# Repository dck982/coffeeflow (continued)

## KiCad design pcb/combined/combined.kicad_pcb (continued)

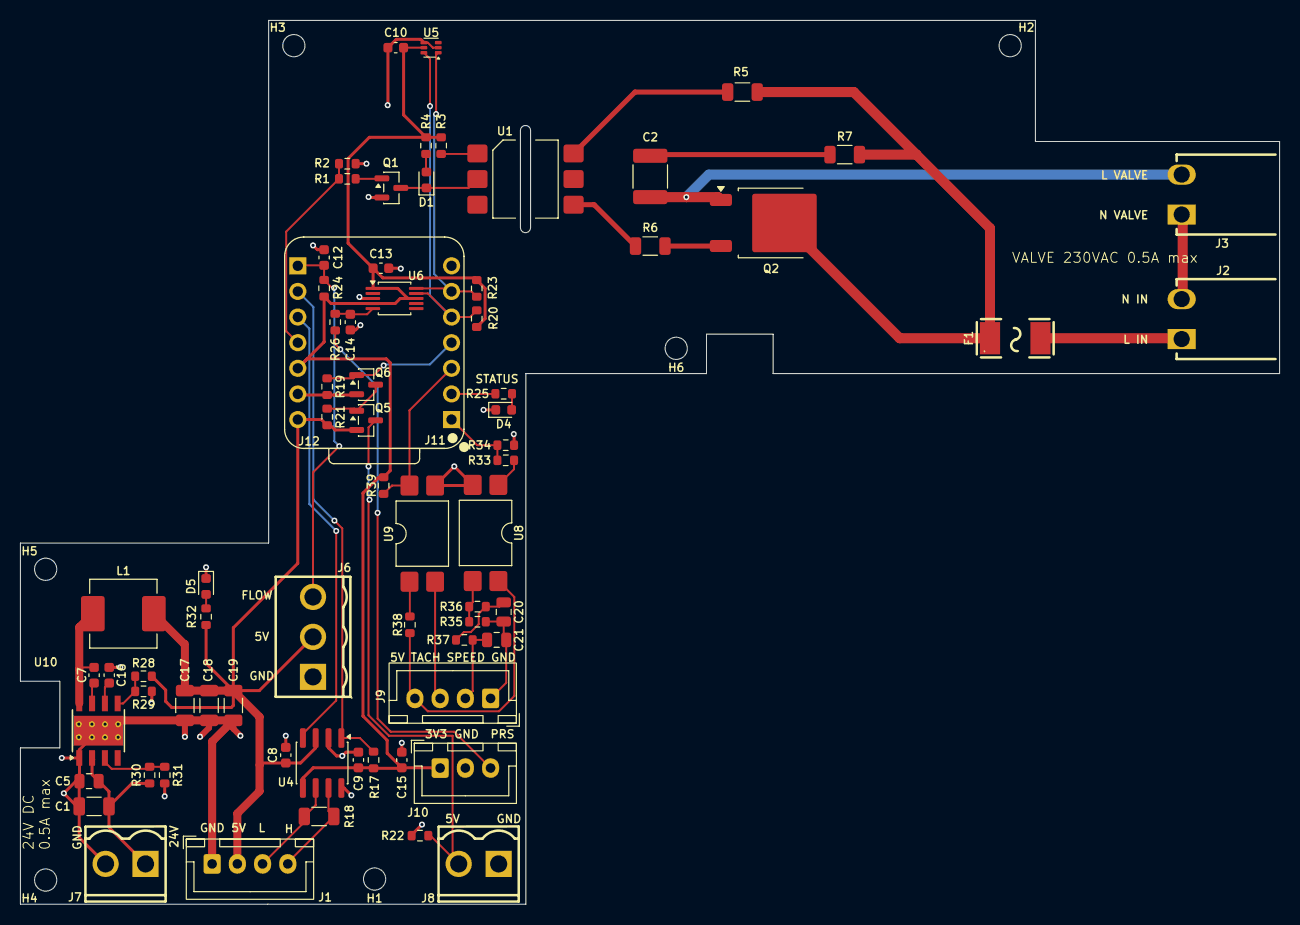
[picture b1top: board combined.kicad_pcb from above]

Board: 2 copper layers, 124.8 x 87.6 mm, 79 parts (0 on the bottom side), 47 nets.

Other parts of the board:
XIAO: XIAO-ESP32-S3-Outline

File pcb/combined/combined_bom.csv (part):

"Reference","Value","Footprint","DNP","MPN","LCSC","Note"
"C1","10uF 50V","Capacitor_SMD:C_1206_3216Metric","","CL31A106KBHNNNE","C13585","VIN ceramic, X5R 50 V 1206"
"C2","10nF 1kV","Capacitor_SMD:C_1812_4532Metric","","FV43X103K102EFG","C394164","Snubber, X7R 1000 V"
"C5","220nF","Capacitor_SMD:C_0805_2012Metric","","CL21B224KBFNNNE","C5378","VIN high-frequency bypass, 50 V X7R 0805, next to the VIN and PGND pins"
"C7","100nF","Capacitor_SMD:C_0603_1608Metric","","CC0603KRX7R9BB104","C14663","BOOT to SW"
"C8","100nF","Capacitor_SMD:C_0603_1608Metric","","CC0603KRX7R9BB104","C14663","Unpolarized capacitor"
"C9","100nF","Capacitor_SMD:C_0603_1608Metric","","CC0603KRX7R9BB104","C14663","Unpolarized capacitor"
"C10","100nF","Capacitor_SMD:C_0603_1608Metric","","CC0603KRX7R9BB104","C14663","Unpolarized capacitor"
"C12","10nF","Capacitor_SMD:C_0603_1608Metric","","0603B103K500NT","C57112","Unpolarized capacitor"
"C13","100nF","Capacitor_SMD:C_0603_1608Metric","","CC0603KRX7R9BB104","C14663","100nF 50V X7R 0603; U6 ADS1115 decoupling."
"C14","10uF","Capacitor_SMD:C_0603_1608Metric","","CL10A106KP8NNNC","C19702","10uF 10V X5R 0603; pressure input filter with R26 (16 Hz)."
"C15","100nF","Capacitor_SMD:C_0603_1608Metric","","CC0603KRX7R9BB104","C14663","100nF 50V X7R 0603; decoupling at the J10 pressure sensor supply."
"C16","1uF","Capacitor_SMD:C_0603_1608Metric","","CL10A105KB8NNNC","C15849","VCC (internal LDO) decoupling"
"C17","22uF","Capacitor_SMD:C_1206_3216Metric","","CL31A226KAHNNNE","C12891","Output ceramic, X5R 25 V 1206"
"C18","22uF","Capacitor_SMD:C_1206_3216Metric","","CL31A226KAHNNNE","C12891","Output ceramic, X5R 25 V 1206"
"C19","22uF","Capacitor_SMD:C_1206_3216Metric","","CL31A226KAHNNNE","C12891","Output ceramic, X5R 25 V 1206"
"C20","2.2uF","Capacitor_SMD:C_0805_2012Metric","","CL21A225KBQNNNE","C377773","Setpoint filter, 50 V X5R"
"C21","2.2uF","Capacitor_SMD:C_0805_2012Metric","","CL21A225KBQNNNE","C377773","Setpoint filter, 50 V X5R"
"D1","RED","LED_SMD:LED_0603_1608Metric","","KT-0603R","C2286","Channel indicator"
"D4","STATUS","LED_SMD:LED_0603_1608Metric","","KT-0603R","C2286","Red 0603, as D1 and D2; pin 1 cathode to GND, pin 2 anode via R25 (1k) from GPIO2."
"D5","5V","LED_SMD:LED_0603_1608Metric","","KT-0603R","C2286","Red 0603, lit while +5V is up"
"F1","0.5A 250V fast","Combined_Local:F2410","","MF2410F0.500TM","C91409","AEM 2410 fast, 100 A breaking at 250 VAC; valve only (65 mA)"
"J1","SCREEN","Connector_JST:JST_XH_B4B-XH-A_1x04_P2.50mm_Vertical","","B4B-XH-A(LF)(SN)","C144395","5 V and CAN to the screen, one cable: 1 GND, 2 +5V, 3 CAN_L, 4 CAN_H"
"J2","MAINS_IN","Combined_Local:CONN-TH_P3.96_HT396R-3.96-2P","","MXHT396R-3.96-02P-OE01-Cu-A","C48688287","1 L, 2 N"
"J3","VALVE","Combined_Local:CONN-TH_P3.96_HT396R-3.96-2P","","MXHT396R-3.96-02P-OE01-Cu-A","C48688287","1 N, 2 L (switched): N next to N of J2"
"J6","FLOW HALL","Combined_Local:CONN-TH_P3.96_HT396V-3.96-3P","","HT396V-3.96-3P","C577789","Kefa HT396V vertical header; mating plug HT396K-3.96-3P (C577778, screw) takes the 0.5 mm2 wires of the Digmesa cable: 1 GND, 2 +5V, 3 FLOW_PULSE"
"J7","24V IN","Combined_Local:CONN-TH_P3.96_HT396V-3.96-2P","","HT396V-3.96-2P","C577788","Kefa HT396V vertical header; mating plug HT396K-3.96-2P (C577777, screw), 1 GND, 2 +24V, from the Wago split of the 24 V supply"
"J8","BOILER SSR","Combined_Local:CONN-TH_P3.96_HT396V-3.96-2P","","HT396V-3.96-2P","C577788","Kefa HT396V vertical header; mating plug HT396K-3.96-2P (C577777, screw, up to 1.5 mm2) takes the 0.75 mm2 wires to the boiler SSR: 1 SSR (-), 2 SSR (+)"
"J9","PUMP","Connector_JST:JST_XH_B4B-XH-A_1x04_P2.50mm_Vertical","","B4B-XH-A(LF)(SN)","C144395","1 GND_P (green), 2 SPEED_P (brown), 3 TACHO_P (blue), 4 +5V_P (yellow); pump side only"
"J10","PRESSURE","Connector_JST:JST_XH_B3B-XH-A_1x03_P2.50mm_Vertical","","B3B-XH-A(LF)(SN)","C144394","Pressure sensor input: pin 1 3V3, 2 GND, 3 output."
"J11","XIAO D0-D6","Combined_Local:XIAO_Socket_1x07_P2.54mm_Vertical","","HC-PM254-5.0H-1x7PZ","C27985232","Female 1x7 2.54 mm socket, 5.0 mm high, for XIAO pins 1-7. Soldered by JLCPCB (THT); the XIAO plugs in by hand."
"J12","XIAO D7-5V","Combined_Local:XIAO_Socket_1x07_P2.54mm_Vertical","","HC-PM254-5.0H-1x7PZ","C27985232","Female 1x7 2.54 mm socket, 5.0 mm high, for XIAO pins 8-14. Soldered by JLCPCB (THT); the XIAO plugs in by hand."
"L1","10uH","Inductor_SMD:L_Changjiang_FXL0630","","FXL0630-100-M","C167223","10 uH, 4.5 A saturation, 68 mOhm"
"Q1","SS8050","Package_TO_SOT_SMD:SOT-23","","SS8050 (Y1)","C2150","SOT-23 pinout 1 B, 2 E, 3 C"
"Q2","BT136S","Package_TO_SOT_SMD:TO-252-2","","BT136S","C23427","DPAK: 1 MT1, 2 MT2 (tab), 3 G"
"Q5","AO3401A","Package_TO_SOT_SMD:SOT-23","","AO3401A","C15127","-4.0A Id, -30V Vds, P-Channel MOSFET, SOT-23"
"Q6","2N7002","Package_TO_SOT_SMD:SOT-23","","2N7002","C8545","0.115A Id, 60V Vds, N-Channel MOSFET, SOT-23"
"R1","1k","Resistor_SMD:R_0603_1608Metric","","0603WAF1001T5E","C21190","Base resistor"
"R2","4.7k","Resistor_SMD:R_0603_1608Metric","","0603WAF4701T5E","C23162","Holds the valve channel off while the XIAO is absent or booting"
"R3","150","Resistor_SMD:R_0603_1608Metric","","0603WAF1500T5E","C22808","MOC LED: (3.3-1.2-0.1)/150 = 13 mA typ, >= 9.6 mA worst case"
"R4","1k","Resistor_SMD:R_0603_1608Metric","","0603WAF1001T5E","C21190","Indicator LED ~1.2 mA"
"R5","300","Resistor_SMD:R_1206_3216Metric","","1206W4F3000T5E","C17887","MT2 series resistor; R5 + R6 = 600 ohms"
"R6","300","Resistor_SMD:R_1206_3216Metric","","1206W4F3000T5E","C17887","Gate series resistor; R5 + R6 = 600 ohms"
"R7","100","Resistor_SMD:R_1206_3216Metric","","1206W4F1000T5E","C17901","Snubber"
"R17","10k","Resistor_SMD:R_0603_1608Metric","","0603WAF1002T5E","C25804","Resistor"
"R18","120 / 0.25W","Resistor_SMD:R_1206_3216Metric","","1206W4F1200T5E","C17909","Resistor"
"R19","100k","Resistor_SMD:R_0603_1608Metric","","0603WAF1003T5E","C25803","Resistor"
"R20","4.7k","Resistor_SMD:R_0603_1608Metric","","0603WAF4701T5E","C23162","Resistor"
"R21","10k","Resistor_SMD:R_0603_1608Metric","","0603WAF1002T5E","C25804","Resistor"
"R22","1k","Resistor_SMD:R_0603_1608Metric","","0603WAF1001T5E","C21190","Resistor"
"R23","4.7k","Resistor_SMD:R_0603_1608Metric","","0603WAF4701T5E","C23162","Resistor"
"R24","1k","Resistor_SMD:R_0603_1608Metric","","0603WAF1001T5E","C21190","Resistor"
"R25","1k","Resistor_SMD:R_0603_1608Metric","","0603WAF1001T5E","C21190","Resistor"
"R26","1k","Resistor_SMD:R_0603_1608Metric","","0603WAF1001T5E","C21190","1k 1% 0603; pressure input filter with C14."
"R28","120k","Resistor_SMD:R_0603_1608Metric","","0603WAF1203T5E","C25808","FB divider top: 1.0 V x (1 + 120/30) = 5.00 V"
"R29","30k","Resistor_SMD:R_0603_1608Metric","","0603WAF3002T5E","C22984","FB divider bottom"
"R30","330k","Resistor_SMD:R_0603_1608Metric","","0603WAF3303T5E","C23137","EN divider top: starts at 18.2 V, stops at 16.7 V"
"R31","24k","Resistor_SMD:R_0603_1608Metric","","0603WAF2402T5E","C23352","EN divider bottom"
"R32","1k","Resistor_SMD:R_0603_1608Metric","","0603WAF1001T5E","C21190","5 V LED, about 3 mA"
"R33","330","Resistor_SMD:R_0603_1608Metric","","0603WAF3300T5E","C23138","U8 LED: (3.3-1.2)/330 = 6 mA from GPIO1"
"R34","100k","Resistor_SMD:R_0603_1608Metric","","0603WAF1003T5E","C25803","Holds PUMP_SPEED low while the XIAO is absent or booting: setpoint 0"
"R35","10k","Resistor_SMD:R_0603_1608Metric","","0603WAF1002T5E","C25804","Pulls the setpoint to GND_P while U8 is off"
"R36","1.5k","Resistor_SMD:R_0603_1608Metric","","0603WAF1501T5E","C22843","Setpoint filter, first stage with C20 (48 Hz)"
"R37","1.5k","Resistor_SMD:R_0603_1608Metric","","0603WAF1501T5E","C22843","Setpoint filter, second stage with C21 (48 Hz)"
"R38","1.8k","Resistor_SMD:R_0603_1608Metric","","0603WAF1801T5E","C4177","U9 LED from the pump 5 V: about 2 mA while blue is low"
"R39","4.7k","Resistor_SMD:R_0603_1608Metric","","0603WAF4701T5E","C23162","PUMP_TACHO pull-up, 0.7 mA"
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
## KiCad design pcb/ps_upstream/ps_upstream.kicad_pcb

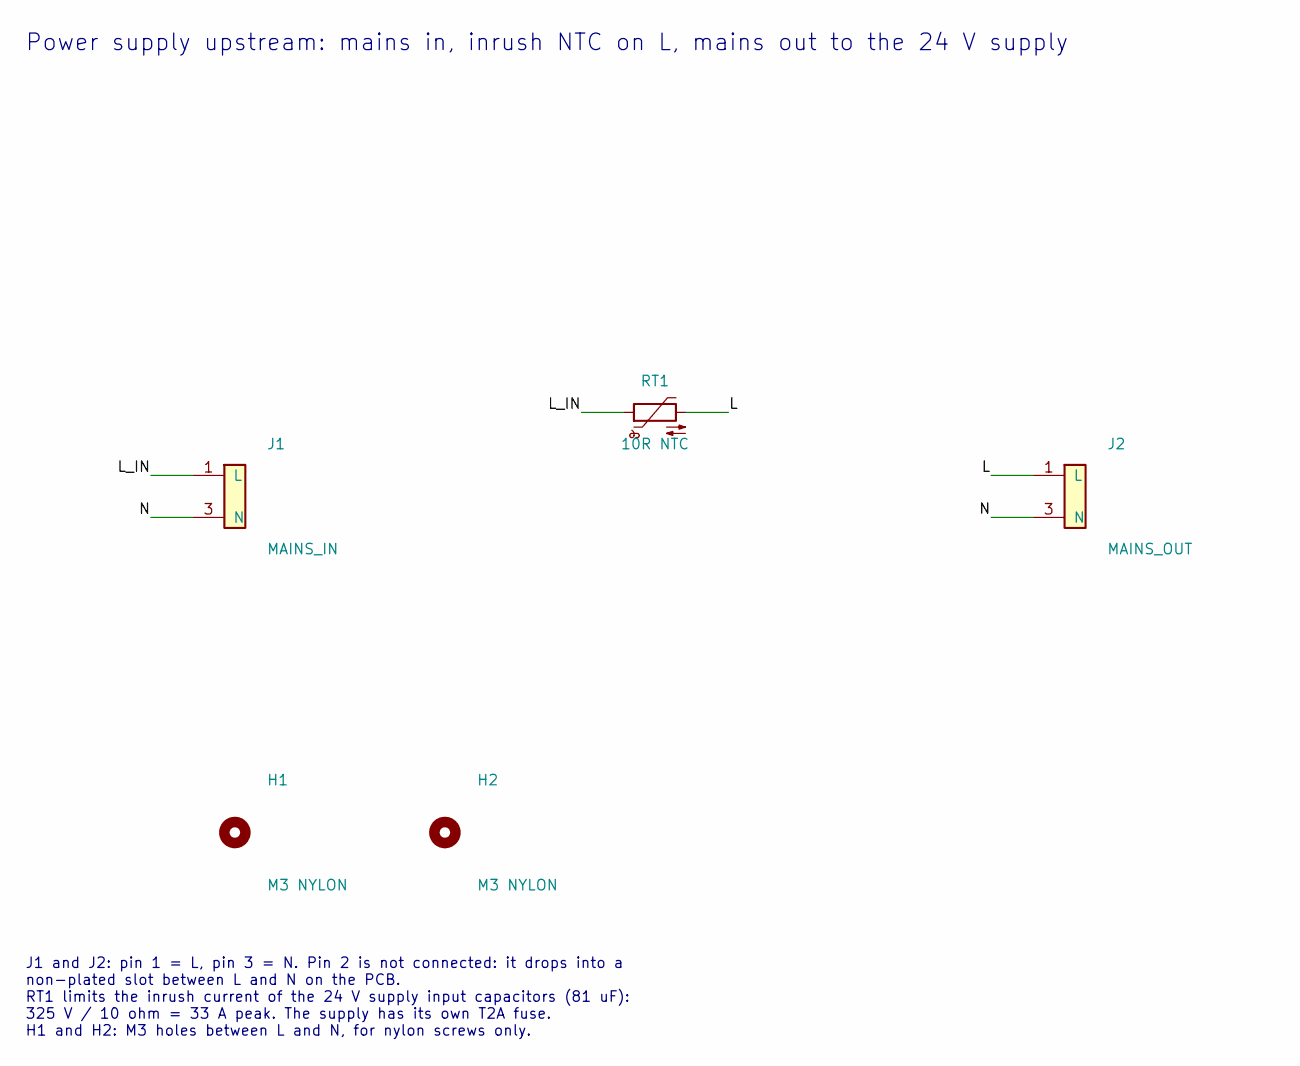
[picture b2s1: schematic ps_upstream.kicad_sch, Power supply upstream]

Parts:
H1, H2: M3 NYLON; MountingHole_3.2mm_M3_Nylon
J1: MAINS_IN; HT396R-3.96-3P_Pin2Slot; MPN HT396R-3.96-3P; LCSC C577800
J2: MAINS_OUT; VH-3A_Pin2Slot; MPN VH-3A; LCSC C20547
RT1: 10R NTC; NTC_TDK_S236_P5.00; MPN B57236S0100M000; LCSC C125458

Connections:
/L: J2.1 (L), RT1.2
/L_IN: J1.1 (L), RT1.1
/N: J1.3 (N), J2.3 (N)

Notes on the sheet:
Power supply upstream: mains in, inrush NTC on L, mains out to the 24 V supply
J1 and J2: pin 1 = L, pin 3 = N. Pin 2 is not connected: it drops into a non-plated slot between L and N on the PCB. RT1 limits the inrush current of the 24 V supply input capacitors (81 uF): 325 V / 10 ohm = 33 A peak. The supply has its own T2A fuse. H1 and H2: M3 holes between L and N, for nylon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

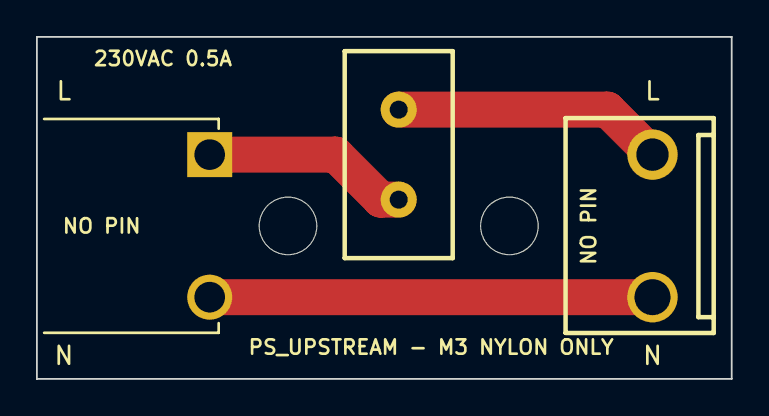
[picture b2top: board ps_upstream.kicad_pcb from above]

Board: 2 copper layers, 38.6 x 19.0 mm, 5 parts (0 on the bottom side), 3 nets.

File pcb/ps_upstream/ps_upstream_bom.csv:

Reference,Value,Footprint,DNP,LCSC,MPN,Description,Note
J1,MAINS_IN,PS_Upstream_Local:HT396R-3.96-3P_Pin2Slot,0,C577800,HT396R-3.96-3P,"Mains input, Kefa HT396R right-angle pluggable header, 3.96 mm","1 L, 2 not connected (slot), 3 N"
RT1,10R NTC,PS_Upstream_Local:NTC_TDK_S236_P5.00,0,C125458,B57236S0100M000,"Inrush current limiter, TDK S236, 10 ohm, 3.5 A, 300 uF tested at 230 V",In series with L
J2,MAINS_OUT,PS_Upstream_Local:VH-3A_Pin2Slot,0,C20547,VH-3A,"Mains output to the 24 V supply, JST VH-compatible vertical header, 3.96 mm","1 L, 2 not connected (slot), 3 N"

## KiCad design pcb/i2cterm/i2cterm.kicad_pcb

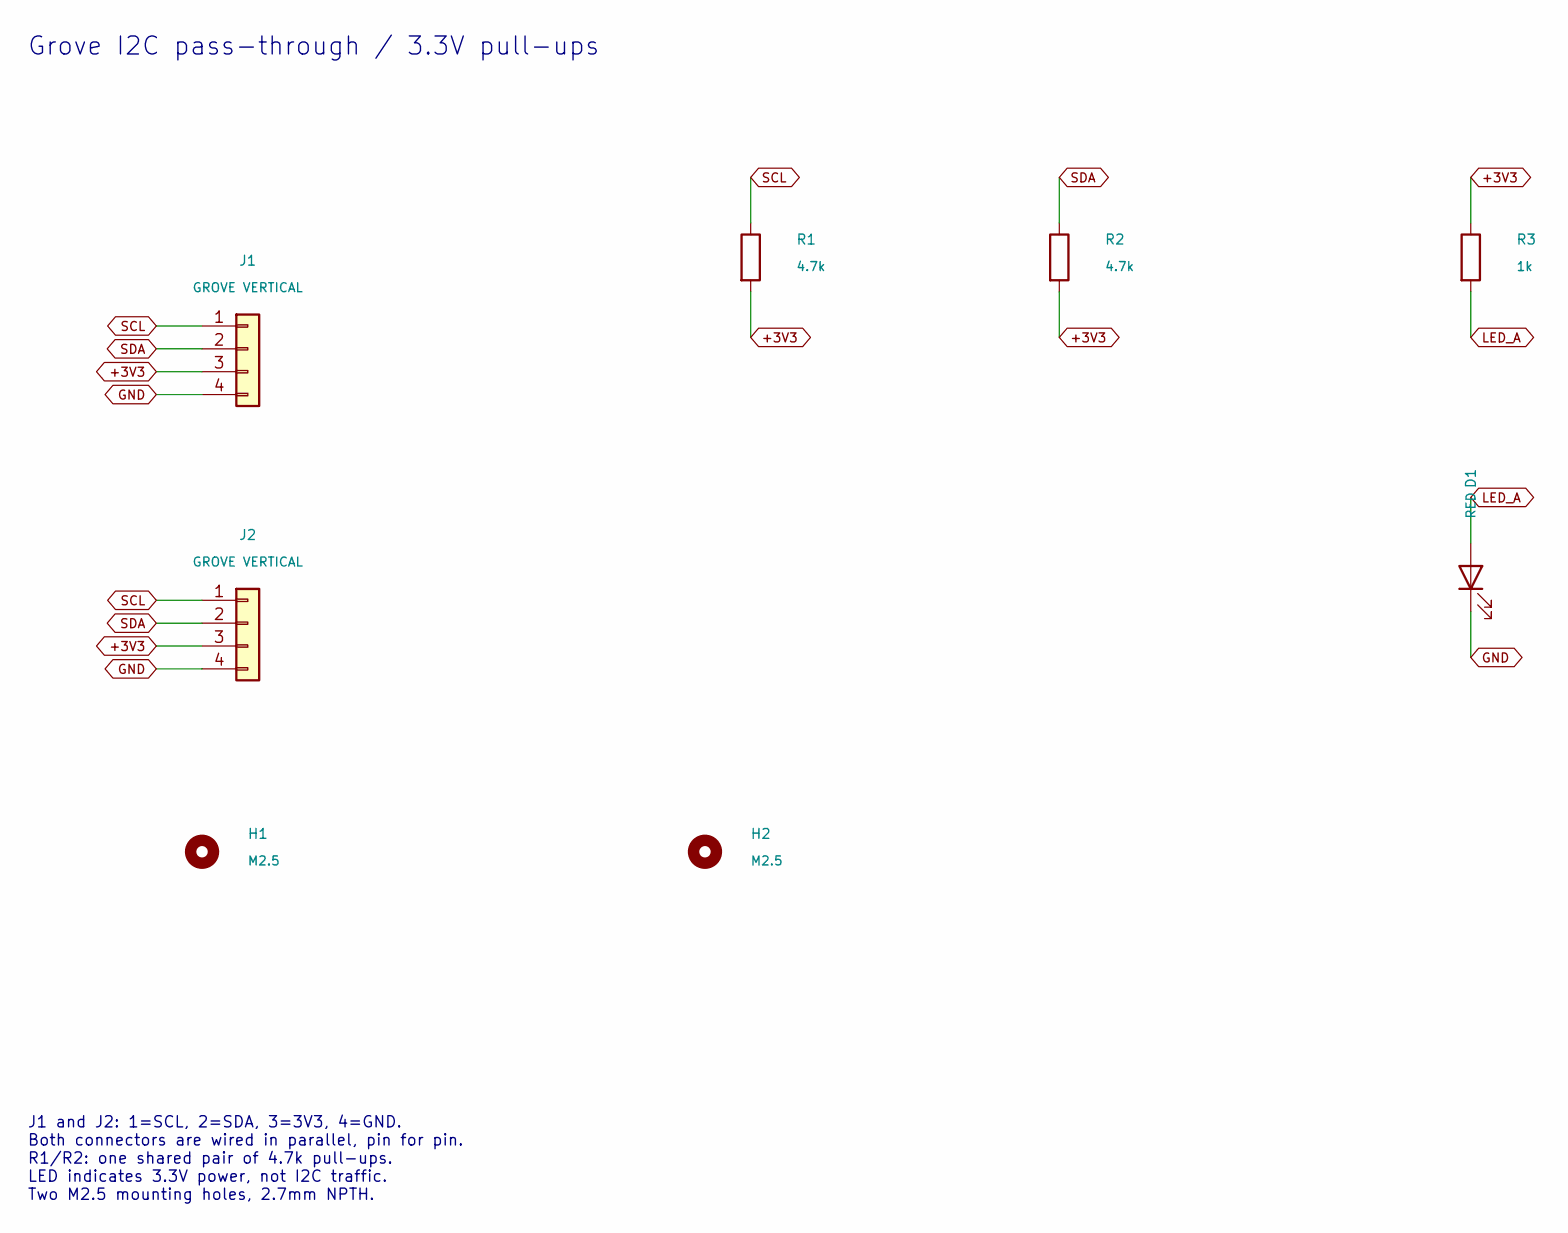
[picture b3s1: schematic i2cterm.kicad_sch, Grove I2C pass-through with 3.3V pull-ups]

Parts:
D1: RED; LED_0603_1608Metric; MPN KT-0603R; LCSC C2286
H1, H2: M2.5; MountingHole_2.7mm_M2.5; MPN M2.5 / 2.7mm
J1, J2: GROVE VERTICAL; CONN-TH_HY-4A; MPN HY-4A; LCSC C722737
R1, R2: 4.7k; R_0603_1608Metric; MPN 0603 4.7k 1%; LCSC C23162
R3: 1k; R_0603_1608Metric; MPN 0603 1k 1%; LCSC C21190

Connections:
+3V3: J1.3, J2.3, R1.2, R2.2, R3.1
GND: D1.1 (K), J1.4, J2.4
LED_A: D1.2 (A), R3.2
SCL: J1.1, J2.1, R1.1
SDA: J1.2, J2.2, R2.1

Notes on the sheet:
Grove I2C pass-through / 3.3V pull-ups
J1 and J2: 1=SCL, 2=SDA, 3=3V3, 4=GND. Both connectors are wired in parallel, pin for pin. R1/R2: one shared pair of 4.7k pull-ups. LED indicates 3.3V power, not I2C traffic. Two M2.5 mounting holes, 2.7mm NPTH.

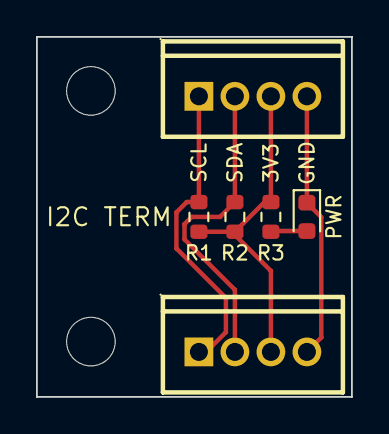
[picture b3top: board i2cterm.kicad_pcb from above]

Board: 2 copper layers, 17.5 x 20.0 mm, 8 parts (0 on the bottom side), 5 nets.

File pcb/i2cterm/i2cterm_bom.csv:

Reference,Value,Footprint,DNP,LCSC,MPN,Description,Sheet,Datasheet
J1,GROVE VERTICAL,I2CTerm_Local:CONN-TH_HY-4A,0,C722737,HY-4A,"Generic connector, single row, 01x04, script generated (kicad-library-utils/schlib/autogen/connector/)",1,https://www.lcsc.com/product-detail/C722737.html
R1,4.7k,Resistor_SMD:R_0603_1608Metric,0,C23162,0603 4.7k 1%,Resistor,1,
R2,4.7k,Resistor_SMD:R_0603_1608Metric,0,C23162,0603 4.7k 1%,Resistor,1,
R3,1k,Resistor_SMD:R_0603_1608Metric,0,C21190,0603 1k 1%,Resistor,1,
D1,RED,LED_SMD:LED_0603_1608Metric,0,C2286,KT-0603R,Light emitting diode,1,https://www.lcsc.com/datasheet/C2286.pdf
J2,GROVE VERTICAL,I2CTerm_Local:CONN-TH_HY-4A,0,C722737,HY-4A,"Generic connector, single row, 01x04, script generated (kicad-library-utils/schlib/autogen/connector/)",1,https://www.lcsc.com/product-detail/C722737.html

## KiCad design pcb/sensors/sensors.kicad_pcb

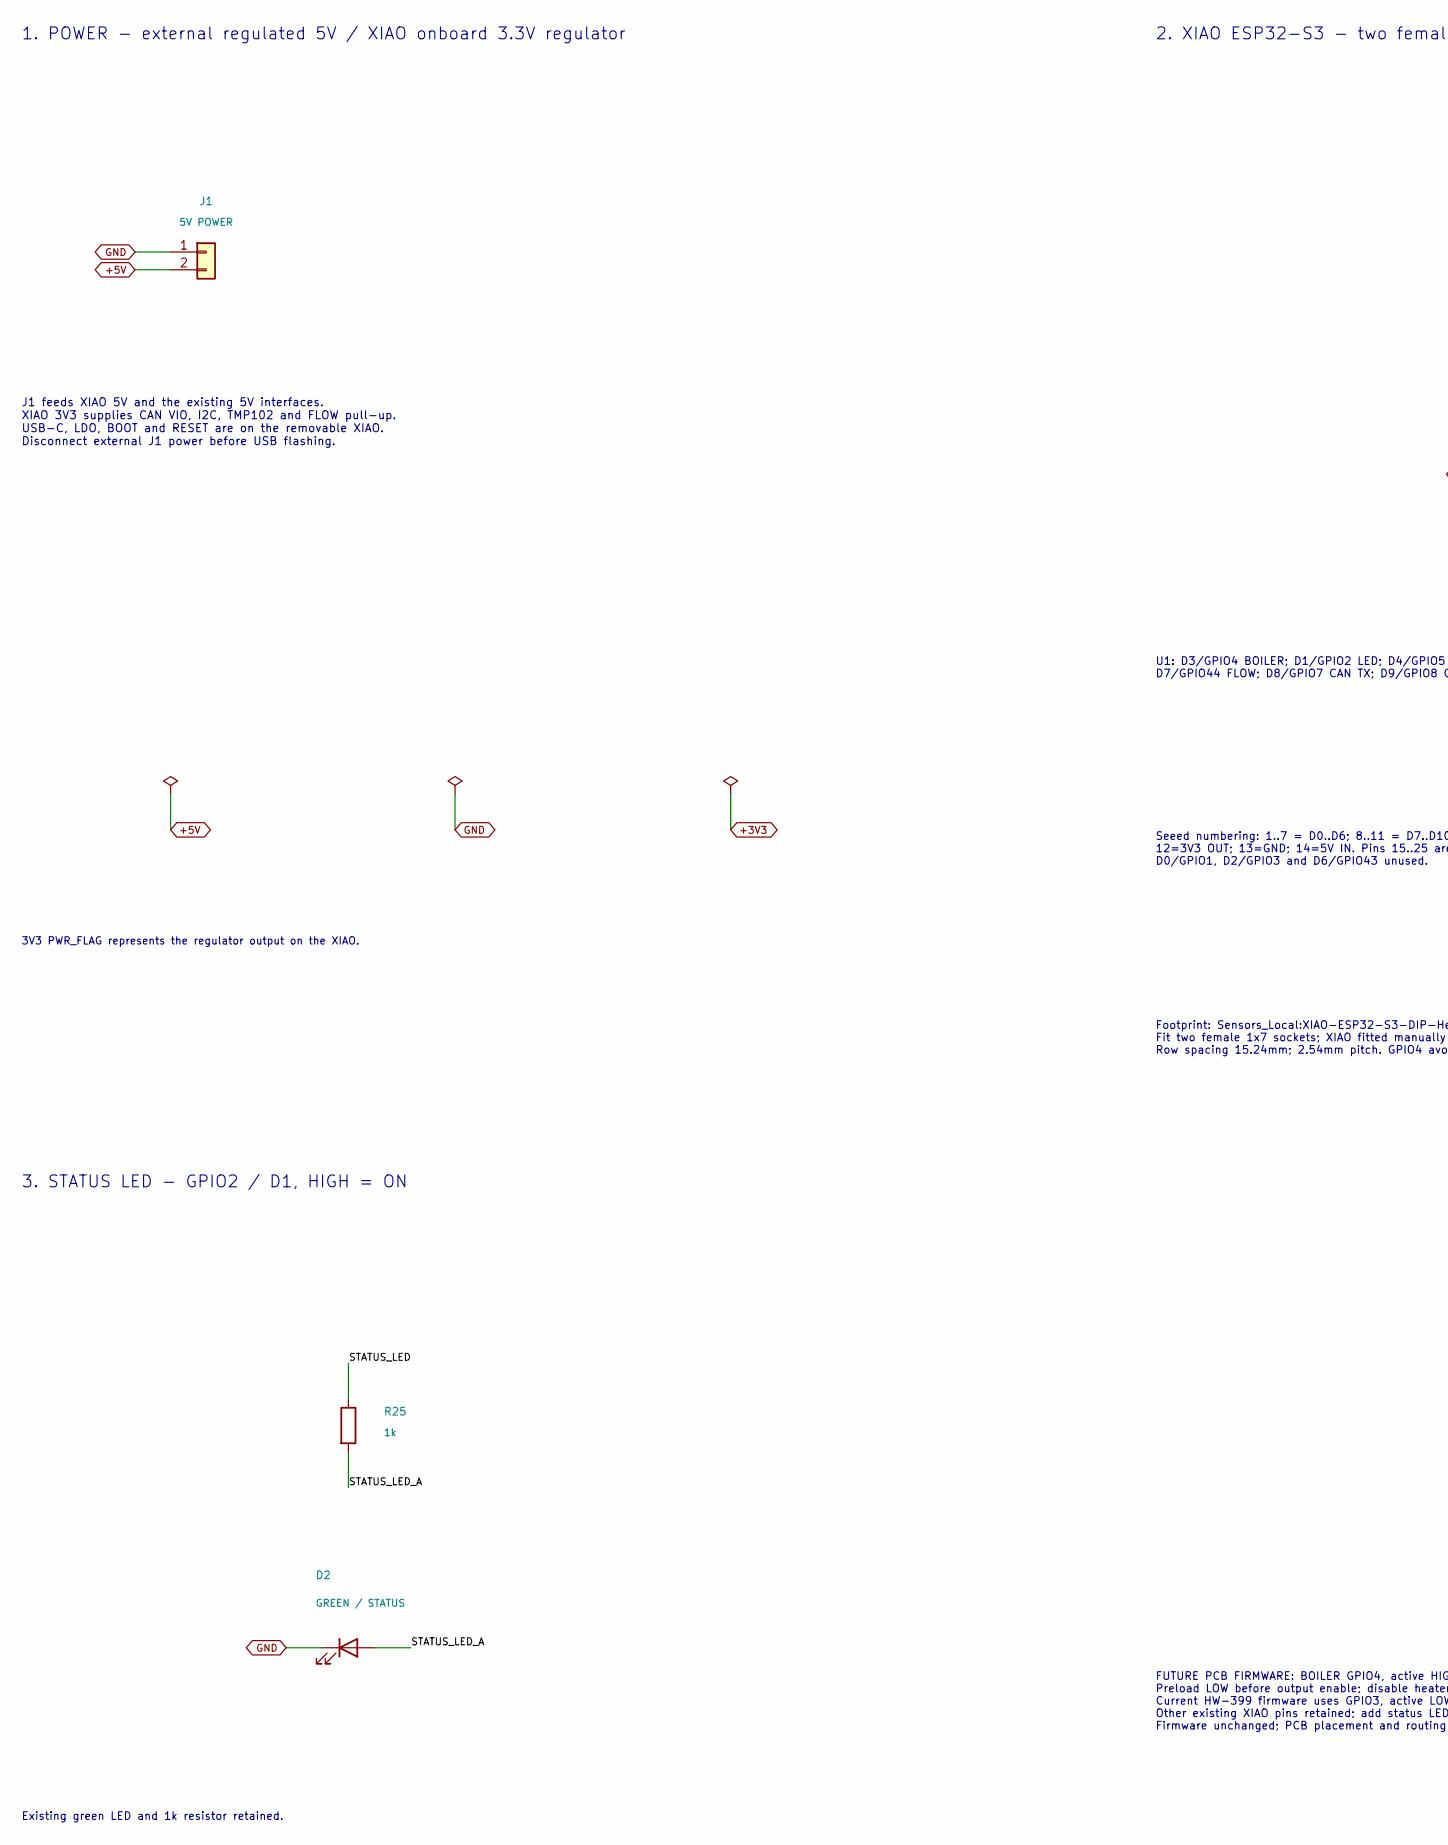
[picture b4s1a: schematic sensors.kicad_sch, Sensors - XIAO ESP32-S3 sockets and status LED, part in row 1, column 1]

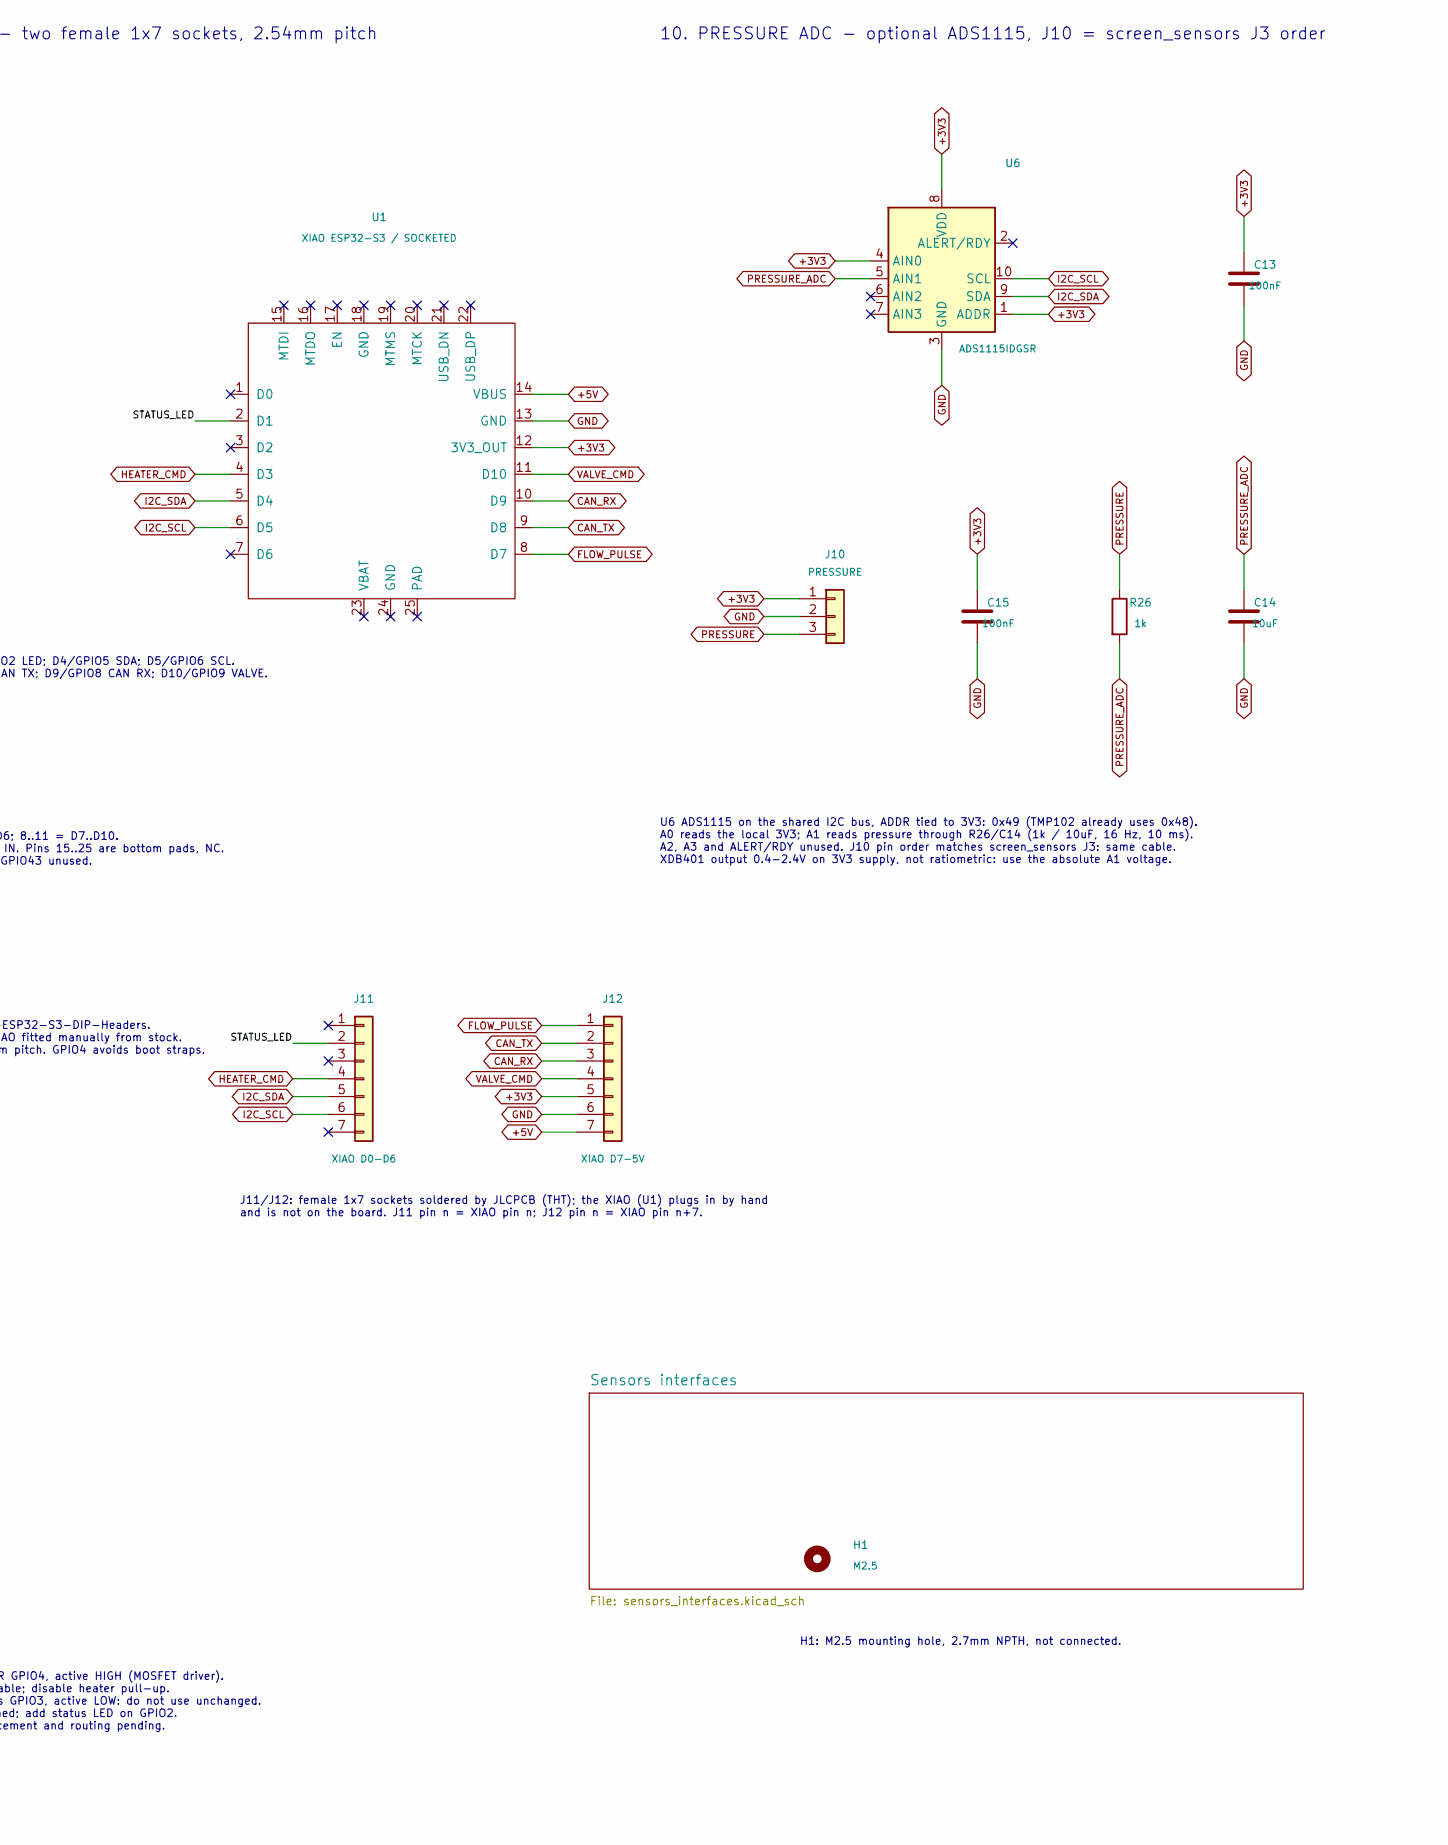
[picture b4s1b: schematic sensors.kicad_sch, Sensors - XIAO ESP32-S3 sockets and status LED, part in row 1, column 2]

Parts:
C13, C15: 100nF; C_0603_1608Metric; MPN CC0603KRX7R9BB104; LCSC C14663
C14: 10uF; C_0603_1608Metric; MPN CL10A106KP8NNNC; LCSC C19702
D2: GREEN / STATUS; LED_0805_2012Metric; MPN KT-0805G; LCSC C2297
H1: M2.5; MountingHole_2.7mm_M2.5; MPN M2.5 / 2.7mm
J1: 5V POWER; JST_XH_B2B-XH-A_1x02_P2.50mm_Vertical; MPN B2B-XH-A(LF)(SN); LCSC C158012
J10: PRESSURE; JST_XH_B3B-XH-A_1x03_P2.50mm_Vertical; MPN B3B-XH-A(LF)(SN); LCSC C144394
J11: XIAO D0-D6; XIAO_Socket_1x07_P2.54mm_Vertical; MPN HX PM2.54-1x7P ZC-Y; LCSC C22438157
J12: XIAO D7-5V; XIAO_Socket_1x07_P2.54mm_Vertical; MPN HX PM2.54-1x7P ZC-Y; LCSC C22438157
R25, R26: 1k; R_0603_1608Metric; MPN 0603WAF1001T5E; LCSC C21190
U1: XIAO ESP32-S3 / SOCKETED; XIAO-ESP32-S3-DIP-Headers; MPN Seeed Studio XIAO ESP32-S3
U6: ADS1115IDGSR; TSSOP-10_3x3mm_P0.5mm; MPN ADS1115IDGSR; LCSC C37593

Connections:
+3V3: C13.1, C15.1, J10.1, J12.5, U1.12 (3V3_OUT), U6.1 (ADDR), U6.4 (AIN0), U6.8 (VDD); also elsewhere on the board
+5V: J1.2, J12.7, U1.14 (VBUS); also elsewhere on the board
/STATUS_LED: J11.2, R25.1, U1.2 (D1)
/STATUS_LED_A: D2.2 (A), R25.2
CAN_RX: J12.3, U1.10 (D9); also elsewhere on the board
CAN_TX: J12.2, U1.9 (D8); also elsewhere on the board
FLOW_PULSE: J12.1, U1.8 (D7); also elsewhere on the board
GND: C13.2, C14.2, C15.2, D2.1 (K), J1.1, J10.2, J12.6, U1.13 (GND), U6.3 (GND); also elsewhere on the board
HEATER_CMD: J11.4, U1.4 (D3); also elsewhere on the board
I2C_SCL: J11.6, U1.6 (D5), U6.10 (SCL); also elsewhere on the board
I2C_SDA: J11.5, U1.5 (D4), U6.9 (SDA); also elsewhere on the board
PRESSURE: J10.3, R26.1
PRESSURE_ADC: C14.1, R26.2, U6.5 (AIN1)
VALVE_CMD: J12.4, U1.11 (D10); also elsewhere on the board

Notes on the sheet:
1. POWER - external regulated 5V / XIAO onboard 3.3V regulator
J1 feeds XIAO 5V and the existing 5V interfaces. XIAO 3V3 supplies CAN VIO, I2C, TMP102 and FLOW pull-up. USB-C, LDO, BOOT and RESET are on the removable XIAO. Disconnect external J1 power before USB flashing.
3V3 PWR_FLAG represents the regulator output on the XIAO.
2. XIAO ESP32-S3 - two female 1x7 sockets, 2.54mm pitch
U1: D3/GPIO4 BOILER; D1/GPIO2 LED; D4/GPIO5 SDA; D5/GPIO6 SCL. D7/GPIO44 FLOW; D8/GPIO7 CAN TX; D9/GPIO8 CAN RX; D10/GPIO9 VALVE.
Seeed numbering: 1..7 = D0..D6; 8..11 = D7..D10. 12=3V3 OUT; 13=GND; 14=5V IN. Pins 15..25 are bottom pads, NC. D0/GPIO1, D2/GPIO3 and D6/GPIO43 unused.
Footprint: Sensors_Local:XIAO-ESP32-S3-DIP-Headers. Fit two female 1x7 sockets; XIAO fitted manually from stock. Row spacing 15.24mm; 2.54mm pitch. GPIO4 avoids boot straps.
3. STATUS LED - GPIO2 / D1, HIGH = ON
Existing green LED and 1k resistor retained.
FUTURE PCB FIRMWARE: BOILER GPIO4, active HIGH (MOSFET driver). Preload LOW before output enable; disable heater pull-up. Current HW-399 firmware uses GPIO3, active LOW: do not use unchanged. Other existing XIAO pins retained; add status LED on GPIO2. Firmware unchanged; PCB placement and routing p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
J11/J12: female 1x7 sockets soldered by JLCPCB (THT); the XIAO (U1) plugs in by hand and is not on the board. J11 pin n = XIAO pin n; J12 pin n = XIAO pin n+7.
H1: M2.5 mounting hole, 2.7mm NPTH, not connected.
10. PRESSURE ADC - optional ADS1115, J10 = screen_sensors J3 order
U6 ADS1115 on the shared I2C bus, ADDR tied to 3V3: 0x49 (TMP102 already uses 0x48). A0 reads the local 3V3; A1 reads pressure through R26/C14 (1k / 10uF, 16 Hz, 10 ms). A2, A3 and ALERT/RDY unused. J10 pin order matches screen_sensors J3: same cable. XDB401 output 0.4-2.4V on 3V3 supply, not ratio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
